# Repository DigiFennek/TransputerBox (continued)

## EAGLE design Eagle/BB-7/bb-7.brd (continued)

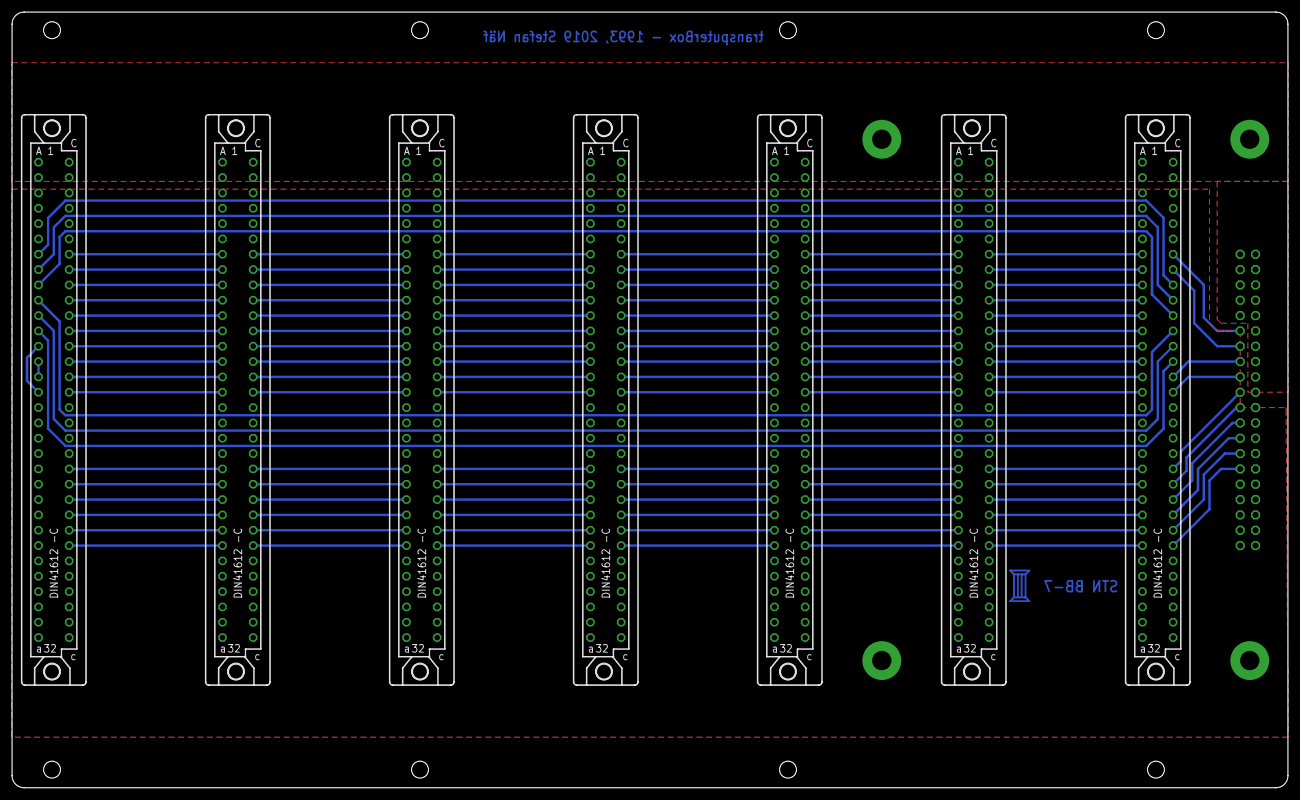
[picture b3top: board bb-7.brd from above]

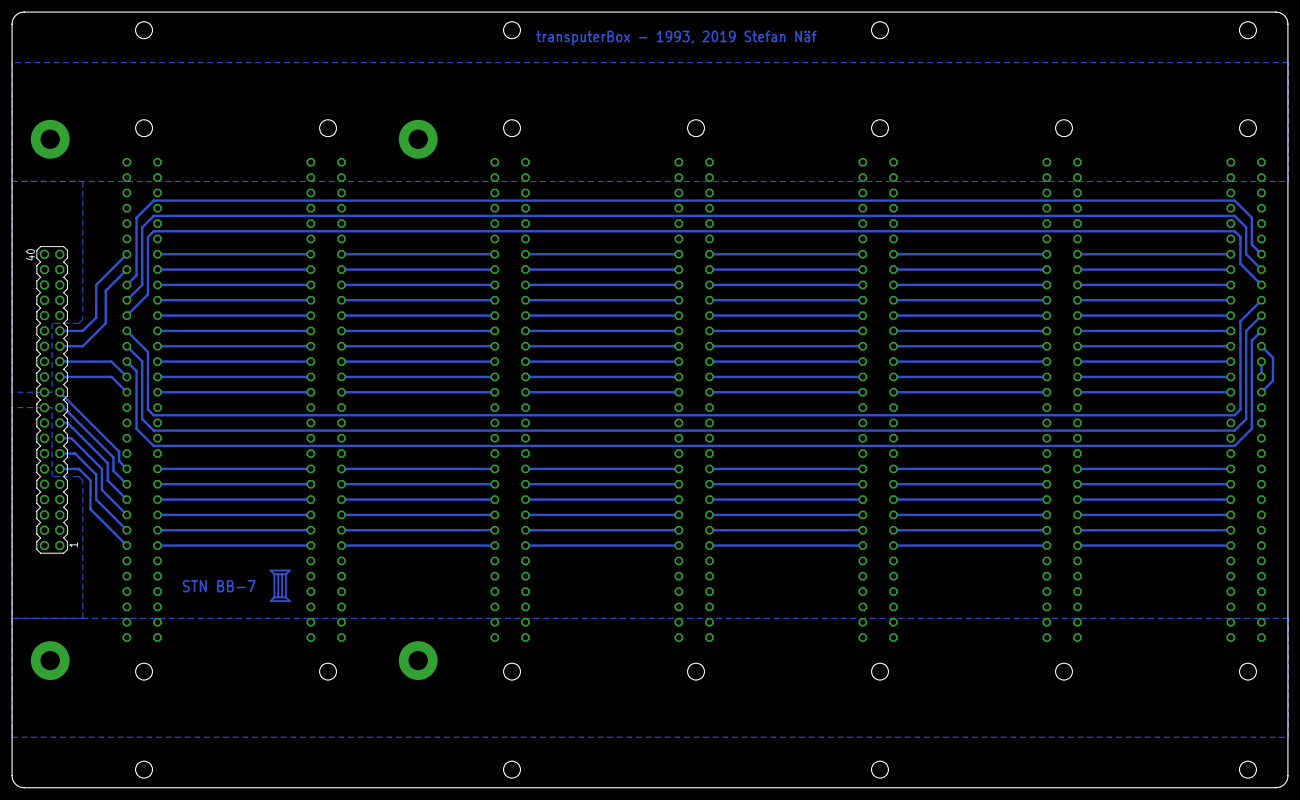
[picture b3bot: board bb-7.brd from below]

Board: 2 copper layers, 211.4 x 128.5 mm, 13 parts (2 on the bottom side), 116 nets.

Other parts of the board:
U$1: LOGO

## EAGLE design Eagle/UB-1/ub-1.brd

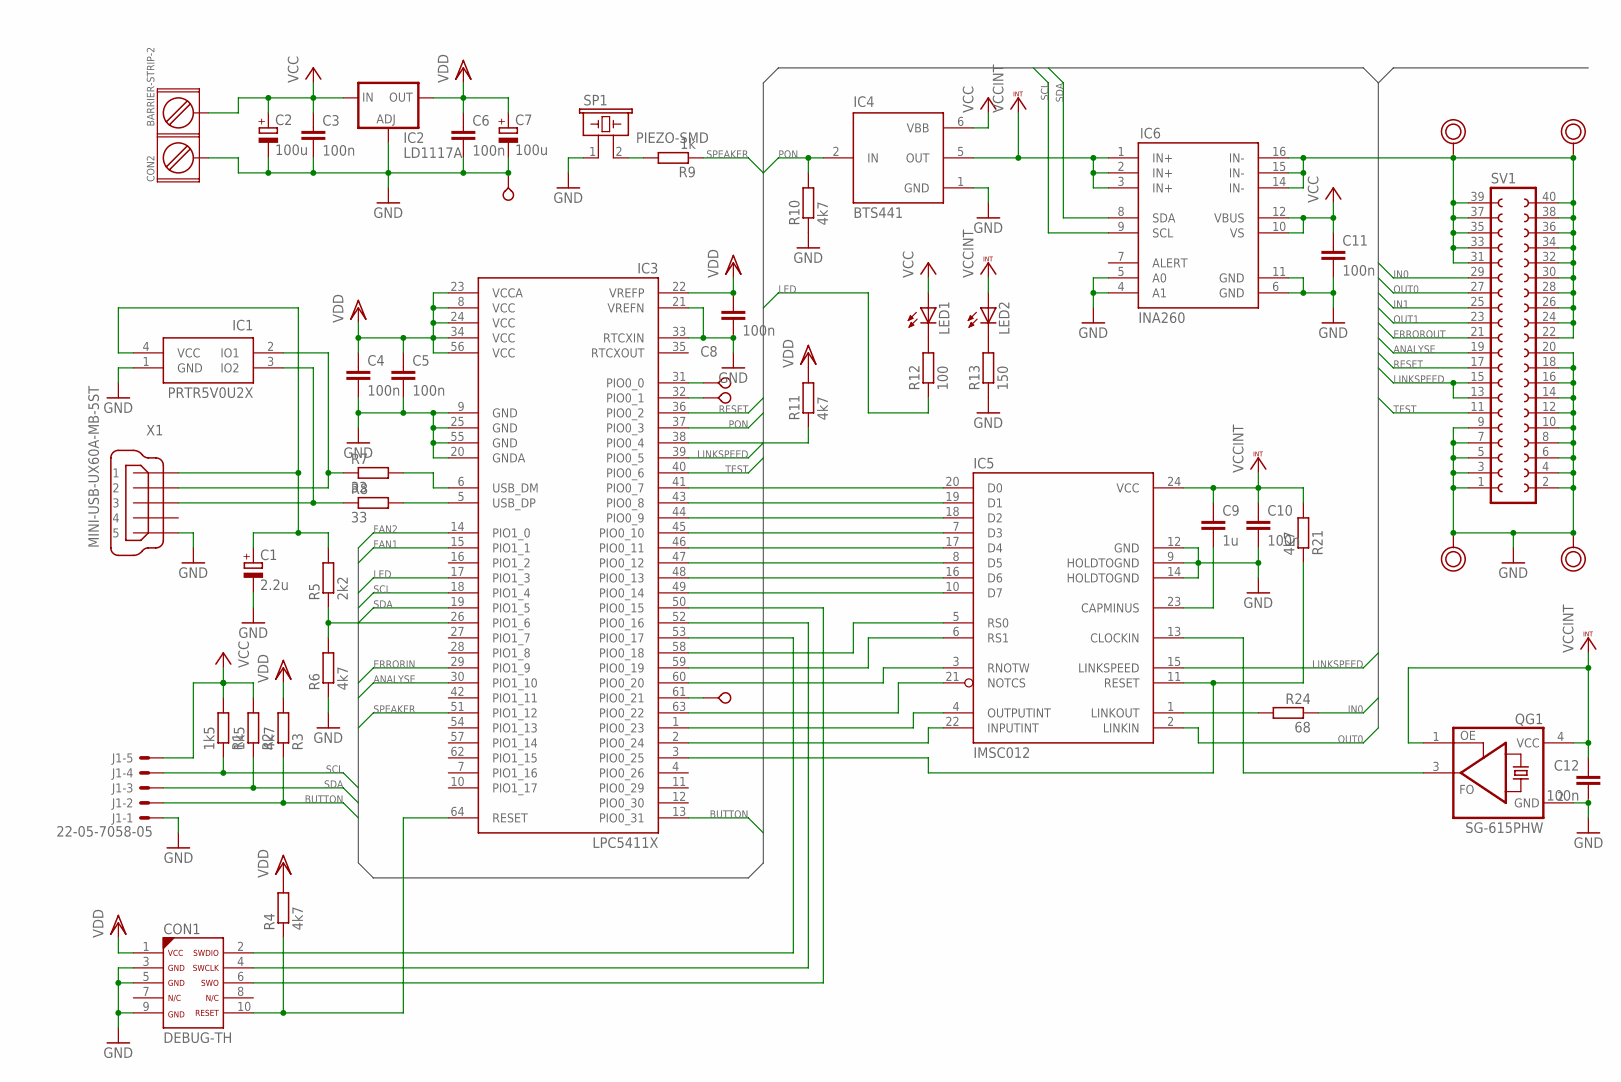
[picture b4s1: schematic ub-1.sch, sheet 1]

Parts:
C1: 2.2u; SMC_B; DIGIKEY 478-3880-1-ND
C2, C7: 100u; SMC_B; DIGIKEY 478-5801-1-ND
C3, C4, C5, C6, C8, C10, C11, C12: 100n; C1206; DIGIKEY 478-10855-1-ND
C9: 1u; C1206; DIGIKEY 478-1567-1-ND
CON1: DEBUG-TH; DIGIKEY 1175-1627-ND
CON2: BARRIER-STRIP-2; DIGIKEY WM13929-ND
IC1: PRTR5V0U2X; SOT143; DIGIKEY 1727-3884-1-ND
IC2: LD1117A; SOT223; DIGIKEY 497-1228-1-ND
IC3: LPC5411X; LQPF64; DIGIKEY 568-13034-ND
IC4: BTS441; TO263-4; DIGIKEY BTS441TGATMA1CT-ND
IC5: IMSC012; DIL24-3
IC6: INA260; TSSOP-16; DIGIKEY 296-47777-1-ND
J1: 22-05-7058-05; 7395-05; DIGIKEY WM2787-ND
LED1, LED2: LEDSMT1206; 1206; DIGIKEY 160-1404-1-ND
QG1: SG-615PHW; SG-615
R1, R2: 1k5; R1206; DIGIKEY CR1206-FX-1501ELFCT-ND
R3, R4, R6, R10, R11, R21: 4k7; R1206; DIGIKEY CR1206-FX-4701ELFCT-ND
R5: 2k2; R1206; DIGIKEY CR1206-FX-2201ELFCT-ND
R7, R8: 33; R1206; DIGIKEY CRS1206-FX-33R0ELFCT-ND
R9: 1k; R1206; DIGIKEY CR1206-FX-1001ELFCT-ND
R12: 100; R1206; DIGIKEY CR1206-FX-1000ELFCT-ND
R13: 150; R1206; DIGIKEY CR1206-FX-1500ELFCT-ND
R24: 68; R1206; DIGIKEY CR1206-FX-68R0ELFCT-ND
SCREW1, SCREW2, SCREW3, SCREW4: POWERPAD
SP1: PIEZO-SMD; DIGIKEY 490-9647-1-ND
SV1: FE20-2
TP1, TP2, TP3, TP4: TESTPOINT; VERO_TP
X1: MINI-USB-UX60A-MB-5ST; UX60A-MB-5ST; DIGIKEY H2961CT-ND

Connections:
ANALYSE: IC3.30 (PIO1_10), SV1.19; also elsewhere on the board
BUTTON: IC3.13 (PIO0_31), J1.2, R3.1
ERRORIN: IC3.29 (PIO1_9); also elsewhere on the board
ERROROUT: SV1.21; also elsewhere on the board
FAN1: IC3.15 (PIO1_1); also elsewhere on the board
FAN2: IC3.14 (PIO1_0); also elsewhere on the board
GND: C1.-, C2.-, C3.2, C4.2, C5.2, C6.2, C7.-, C8.2, C10.2, C11.2, C12.2, CON1.3, CON1.5, CON1.9, CON2.1, IC1.1 (GND), IC2.1 (ADJ), IC3.9 (GND), IC3.20 (GNDA), IC3.21 (VREFN), IC3.25 (GND), IC3.33 (RTCXIN), IC3.55 (GND), IC4.1 (GND), IC5.9 (HOLDTOGND), IC5.12 (GND), IC5.14 (HOLDTOGND), IC6.4 (A1), IC6.5 (A0), IC6.6 (GND), IC6.11 (GND), J1.1, QG1.2 (GND), R6.1, R10.1, R13.1, SCREW2.P$1, SCREW4.P$1, SP1.1, SV1.1, SV1.2, SV1.3, SV1.4, SV1.5, SV1.6, SV1.7, SV1.8, SV1.9, SV1.10, SV1.12, SV1.14, SV1.16, SV1.18, SV1.20, TP3.P$1, X1.5; also elsewhere on the board
IN0: R24.1, SV1.29
IN1: SV1.25; also elsewhere on the board
LED: IC3.17 (PIO1_3), R12.1
LINKSPEED: IC3.39 (PIO0_5), IC5.15 (LINKSPEED), SV1.13, SV1.15
unnamed: CON1.2, IC3.53 (PIO0_17)
unnamed: IC3.31 (PIO0_0), TP1.P$1
unnamed: CON1.4, IC3.52 (PIO0_16)
unnamed: CON1.10, IC3.64 (RESET), R4.1
unnamed: IC3.26 (PIO1_6), R5.1, R6.2
unnamed: IC3.5 (USB_DP), R8.2
unnamed: IC3.6 (USB_DM), R7.2
unnamed: IC6.14 (IN-), IC6.15 (IN-), IC6.16 (IN-), SCREW1.P$1, SCREW3.P$1, SV1.22, SV1.24, SV1.26, SV1.28, SV1.30, SV1.31, SV1.32, SV1.33, SV1.34, SV1.35, SV1.36, SV1.37, SV1.38, SV1.39, SV1.40
unnamed: IC3.41 (PIO0_7), IC5.20 (D0)
unnamed: IC3.32 (PIO0_1), TP2.P$1
unnamed: IC3.61 (PIO0_21), TP4.P$1
unnamed: IC5.1 (LINKOUT), R24.2
unnamed: IC3.43 (PIO0_8), IC5.19 (D1)
unnamed: IC3.44 (PIO0_9), IC5.18 (D2)
unnamed: IC3.45 (PIO0_10), IC5.7 (D3)
unnamed: IC3.46 (PIO0_11), IC5.17 (D4)
unnamed: IC3.47 (PIO0_12), IC5.8 (D5)
unnamed: IC3.48 (PIO0_13), IC5.16 (D6)
unnamed: IC3.49 (PIO0_14), IC5.10 (D7)
unnamed: IC3.60 (PIO0_20), IC5.3 (RNOTW)
unnamed: IC3.59 (PIO0_19), IC5.6 (RS1)
unnamed: IC3.58 (PIO0_18), IC5.5 (RS0)
unnamed: IC3.1 (PIO0_23), IC5.4 (OUTPUTINT)
unnamed: IC3.2 (PIO0_24), IC5.22 (INPUTINT)
unnamed: IC3.63 (PIO0_22), IC5.21 (NOTCS)
unnamed: IC5.13 (CLOCKIN), QG1.3 (FO)
unnamed: C9.2, IC5.23 (CAPMINUS)
unnamed: IC1.2 (IO1), R7.1, X1.2
unnamed: IC1.3 (IO2), R8.1, X1.3
unnamed: LED2.C, R13.2
unnamed: R9.2, SP1.2
unnamed: LED1.C, R12.2
unnamed: CON1.6, IC3.50 (PIO0_15)
unnamed: IC3.38 (PIO0_4), R11.1
unnamed: IC3.3 (PIO0_25), IC5.11 (RESET), R21.1
OUT0: IC5.2 (LINKIN), SV1.27
OUT1: SV1.23; also elsewhere on the board
PON: IC3.37 (PIO0_3), IC4.2 (IN), R10.2; also elsewhere on the board
RESET: IC3.36 (PIO0_2), SV1.17; also elsewhere on the board
SCL: IC3.18 (PIO1_4), IC6.9 (SCL), J1.4, R1.1
SDA: IC3.19 (PIO1_5), IC6.8 (SDA), J1.3, R2.1
SPEAKER: IC3.51 (PIO1_12), R9.1
TEST: IC3.40 (PIO0_6), SV1.11
VCC: C2.+, C3.1, C11.1, CON2.2, IC2.3 (IN), IC4.6 (VBB), IC6.10 (VS), IC6.12 (VBUS), J1.5, LED1.A, R1.2, R2.2; also elsewhere on the board
VCCINT: C9.1, C10.1, C12.1, IC4.5 (OUT), IC5.24 (VCC), IC6.1 (IN+), IC6.2 (IN+), IC6.3 (IN+), LED2.A, QG1.1 (OE), QG1.4 (VCC), R21.2; also elsewhere on the board
VDD: C4.1, C5.1, C6.1, C7.+, C8.1, CON1.1, IC2.2 (OUT), IC3.8 (VCC), IC3.22 (VREFP), IC3.23 (VCCA), IC3.24 (VCC), IC3.34 (VCC), IC3.56 (VCC), R3.2, R4.2, R11.2
VUSB: C1.+, IC1.4 (VCC), R5.2, X1.1

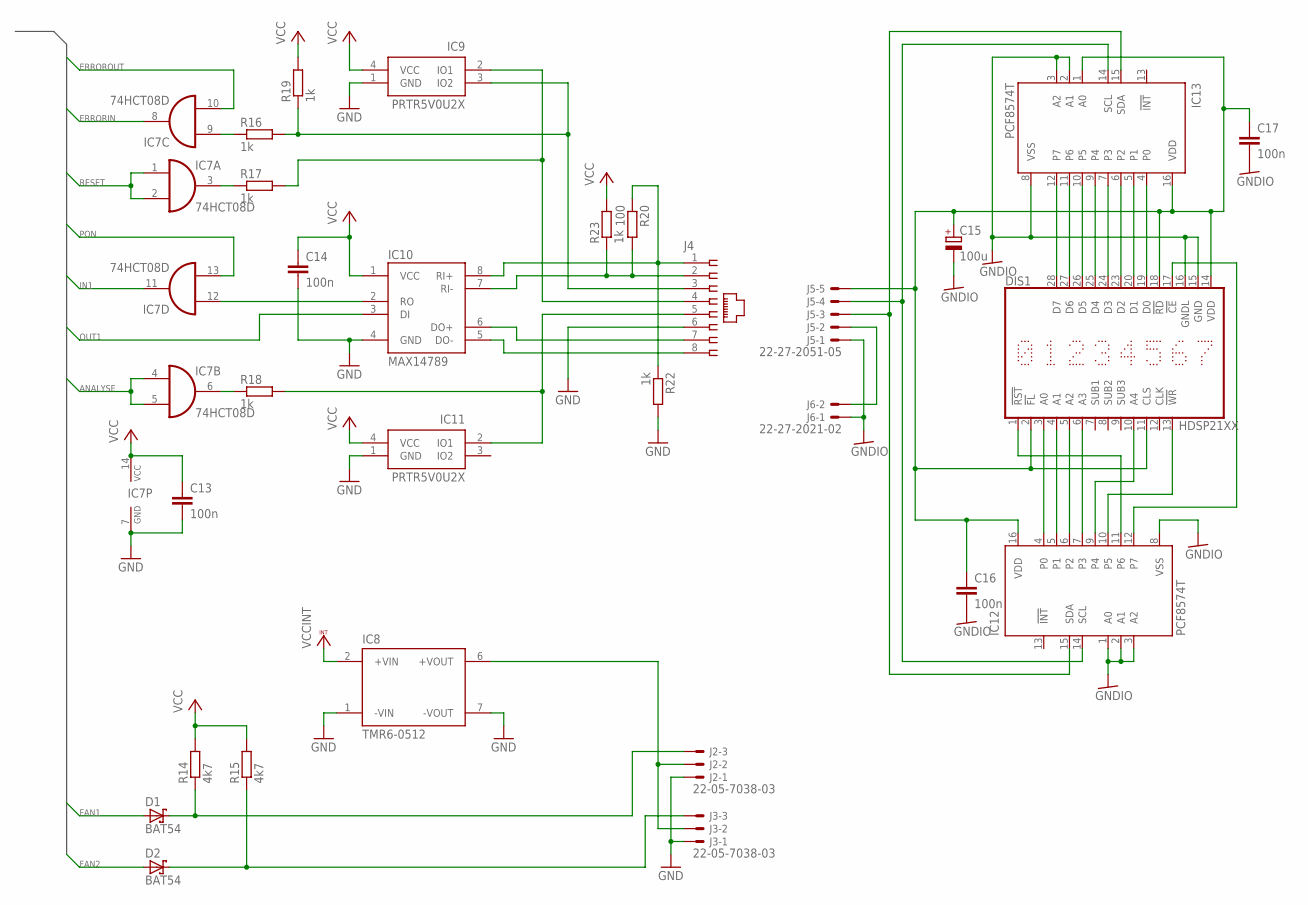
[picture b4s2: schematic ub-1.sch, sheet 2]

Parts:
C13, C14, C16, C17: 100n; C1206; DIGIKEY 478-10855-1-ND
C15: 100u; SMC_B; DIGIKEY 478-5801-1-ND
D1, D2: BAT54; SOT23; DIGIKEY BAT54FSCT-ND
DIS1: HDSP21XX; DIGIKEY 516-1161-5-ND
IC7: 74HCT08D; SO14; DIGIKEY 296-14862-1-ND
IC8: TMR6-0512; DIGIKEY 1951-2391-ND
IC9, IC11: PRTR5V0U2X; SOT143; DIGIKEY 1727-3884-1-ND
IC10: MAX14789; SO8; DIGIKEY MAX14789EGSA+-ND
IC12, IC13: PCF8574T; SO16W; DIGIKEY 568-1077-1-ND
J2, J3: 22-05-7038-03; 7395-03; DIGIKEY WM2785-ND
J4: 555164-1; DIGIKEY A31442-ND
J5: 22-27-2051-05; 6410-05; DIGIKEY WM4114-ND
J6: 22-27-2021-02; 6410-02; DIGIKEY WM4111-ND
R14, R15: 4k7; R1206; DIGIKEY CR1206-FX-4701ELFCT-ND
R16, R17, R18, R19, R22, R23: 1k; R1206; DIGIKEY CR1206-FX-1001ELFCT-ND
R20: 100; R1206; DIGIKEY CR1206-FX-1000ELFCT-ND

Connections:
ANALYSE: IC7.4 (I0), IC7.5 (I1); also elsewhere on the board
ERRORIN: IC7.8 (O); also elsewhere on the board
ERROROUT: IC7.10 (I1); also elsewhere on the board
FAN1: D1.1 (A); also elsewhere on the board
FAN2: D2.1 (A); also elsewhere on the board
GND: C13.2, C14.2, IC7.7 (GND), IC8.1 (-VIN), IC8.7 (-VOUT), IC9.1 (GND), IC10.4 (GND), IC11.1 (GND), J2.1, J3.1, J4.6, R22.2; also elsewhere on the board
GNDIO: C15.-, C16.2, C17.2, DIS1.15 (GND), DIS1.16 (GNDL), IC12.1 (A0), IC12.2 (A1), IC12.3 (A2), IC12.8 (VSS), IC13.2 (A1), IC13.3 (A2), IC13.8 (VSS), J5.1, J6.1
IN1: IC7.11 (O); also elsewhere on the board
unnamed: DIS1.3 (A0), IC12.4 (P0)
unnamed: DIS1.19 (D0), IC13.4 (P0)
unnamed: DIS1.20 (D1), IC13.5 (P1)
unnamed: DIS1.23 (D2), IC13.6 (P2)
unnamed: DIS1.24 (D3), IC13.7 (P3)
unnamed: DIS1.25 (D4), IC13.9 (P4)
unnamed: DIS1.26 (D5), IC13.10 (P5)
unnamed: DIS1.27 (D6), IC13.11 (P6)
unnamed: DIS1.28 (D7), IC13.12 (P7)
unnamed: DIS1.4 (A1), IC12.5 (P1)
unnamed: DIS1.5 (A2), IC12.6 (P2)
unnamed: DIS1.6 (A3), IC12.7 (P3)
unnamed: DIS1.10 (A4), IC12.9 (P4)
unnamed: J5.2, J6.2
unnamed: C15.+, C16.1, C17.1, DIS1.2 (!FL), DIS1.11 (CLS), DIS1.14 (VDD), DIS1.18 (!RD), IC12.16 (VDD), IC13.1 (A0), IC13.16 (VDD), J5.5
unnamed: DIS1.1 (!RST), IC12.11 (P6)
unnamed: DIS1.13 (!WR), IC12.10 (P5)
unnamed: IC12.14 (SCL), IC13.14 (SCL), J5.4
unnamed: DIS1.17 (!CE), IC12.12 (P7)
unnamed: IC12.15 (SDA), IC13.15 (SDA), J5.3
unnamed: IC10.8 (RI+), J4.1, R20.1, R22.1
unnamed: IC10.7 (RI-), J4.2, R20.2, R23.1
unnamed: IC10.5 (DO-), J4.8
unnamed: IC10.6 (DO+), J4.7
unnamed: IC7.6 (O), R18.1
unnamed: IC7.3 (O), R17.1
unnamed: IC7.9 (I0), R16.1
unnamed: IC9.3 (IO2), J4.3, R16.2, R19.1
unnamed: IC9.2 (IO1), J4.4, R17.2
unnamed: IC11.2 (IO1), J4.5, R18.2
unnamed: IC7.12 (I0), IC10.2 (RO)
unnamed: D2.3 (C), J3.3, R15.1
unnamed: D1.3 (C), J2.3, R14.1
unnamed: IC8.6 (+VOUT), J2.2, J3.2
OUT1: IC10.3 (DI); also elsewhere on the board
PON: IC7.13 (I1); also elsewhere on the board
RESET: IC7.1 (I0), IC7.2 (I1); also elsewhere on the board
VCC: C13.1, C14.1, IC7.14 (VCC), IC9.4 (VCC), IC10.1 (VCC), IC11.4 (VCC), R14.2, R15.2, R19.2, R23.2; also elsewhere on the board
VCCINT: IC8.2 (+VIN); also elsewhere on the board

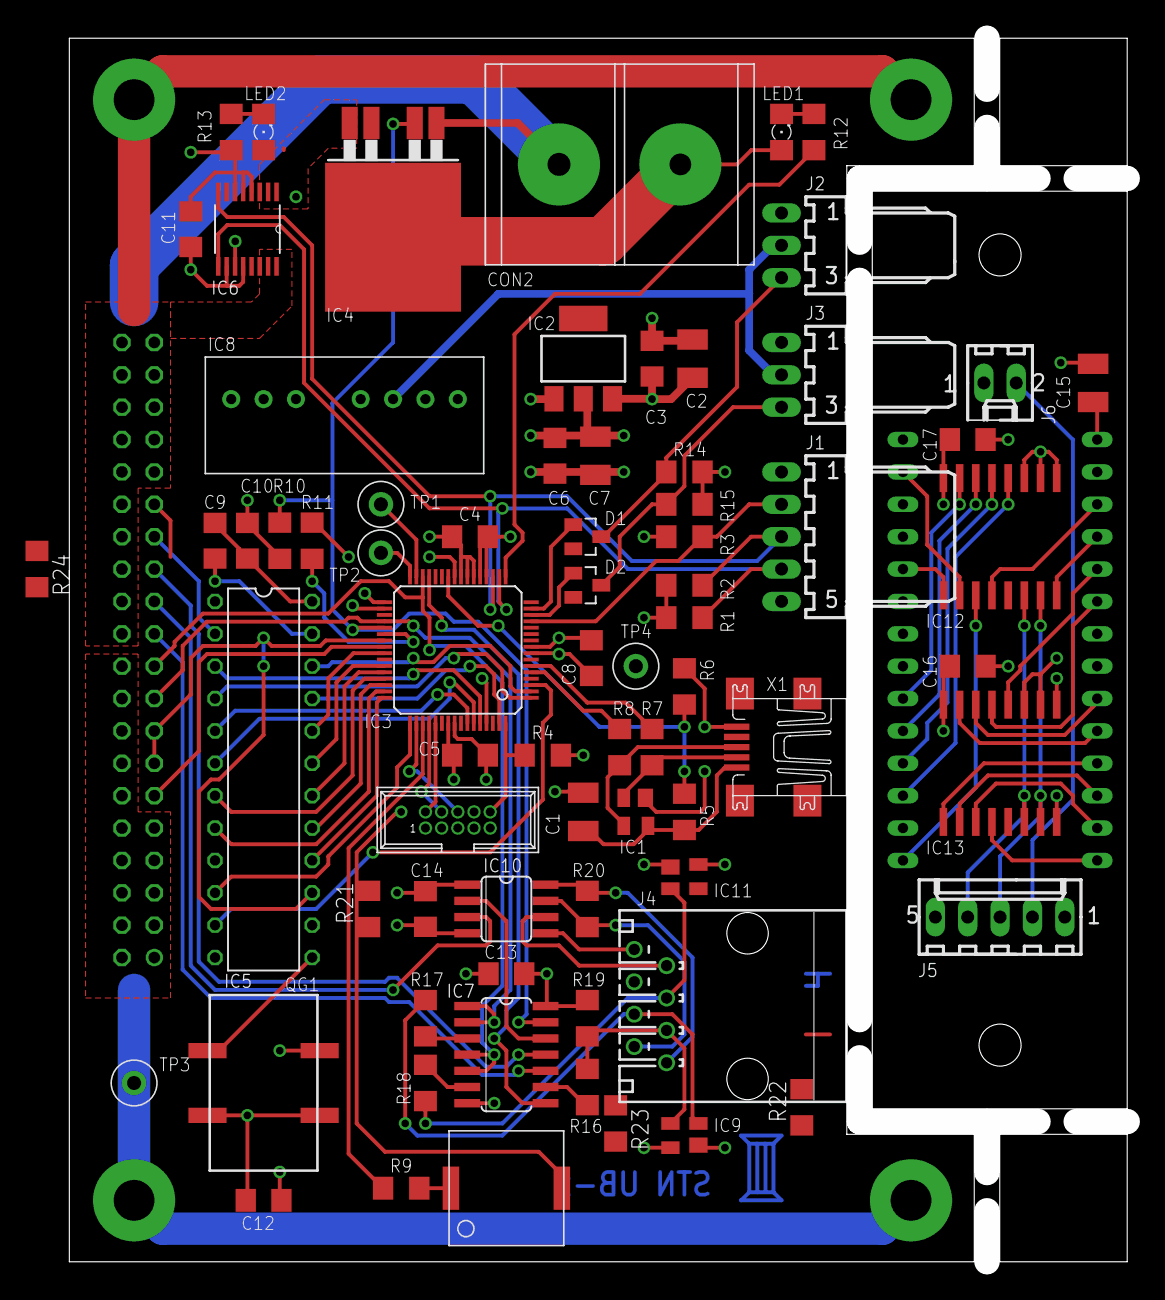
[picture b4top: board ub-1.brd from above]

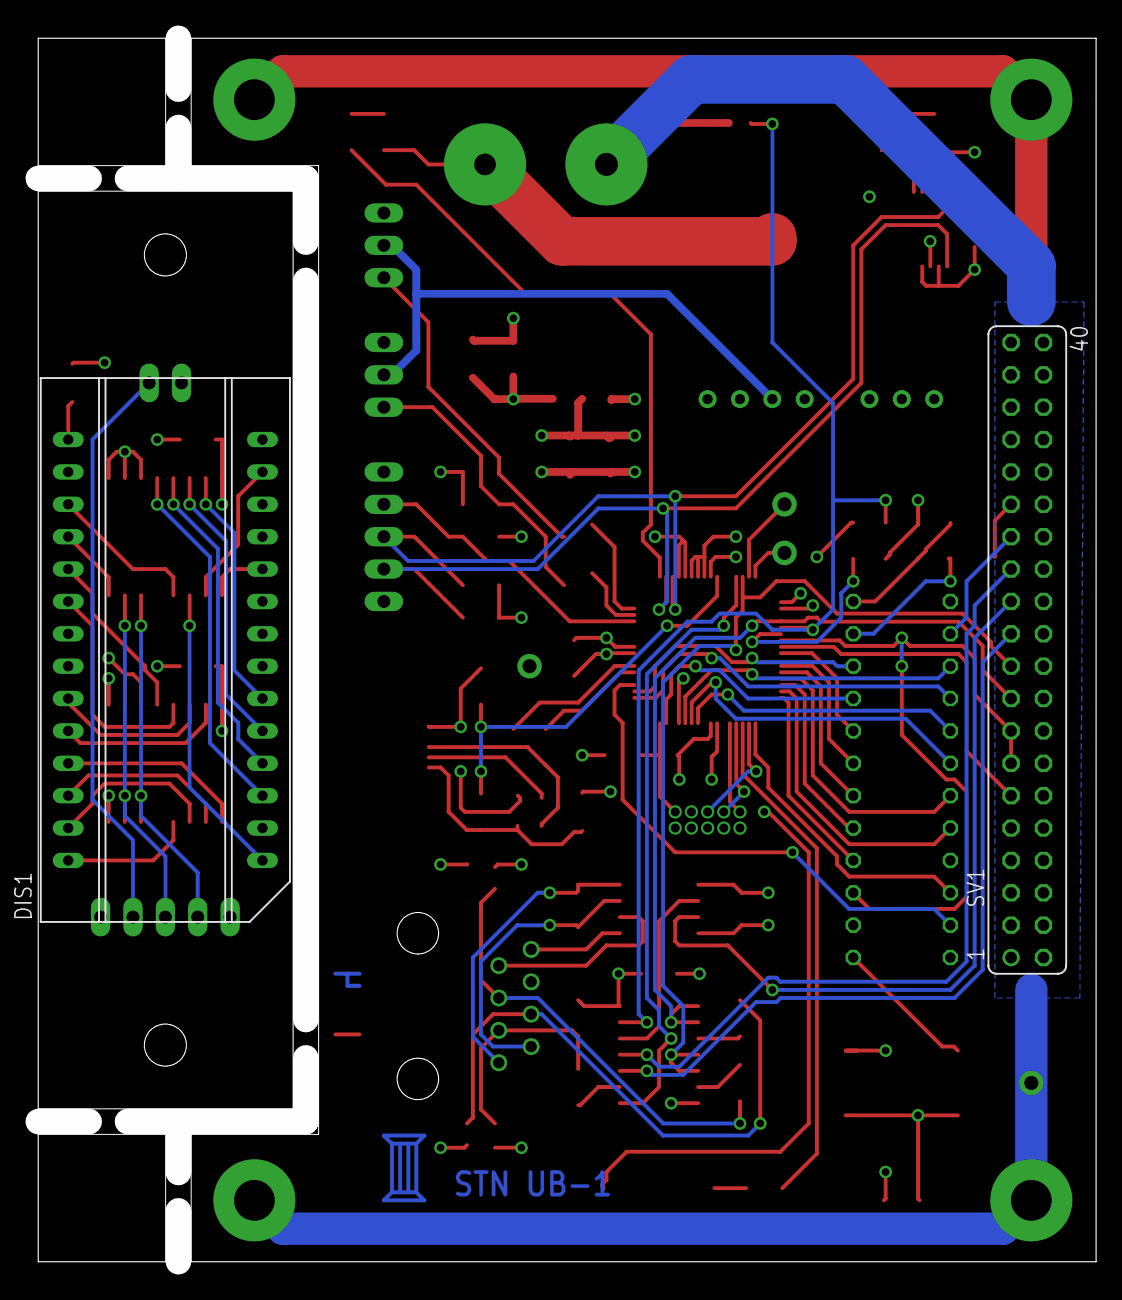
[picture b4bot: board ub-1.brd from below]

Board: 4 copper layers, 83.0 x 96.0 mm, 81 parts (3 on the bottom side), 93 nets.

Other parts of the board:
U$5: LAYER14
U$6: LOGO

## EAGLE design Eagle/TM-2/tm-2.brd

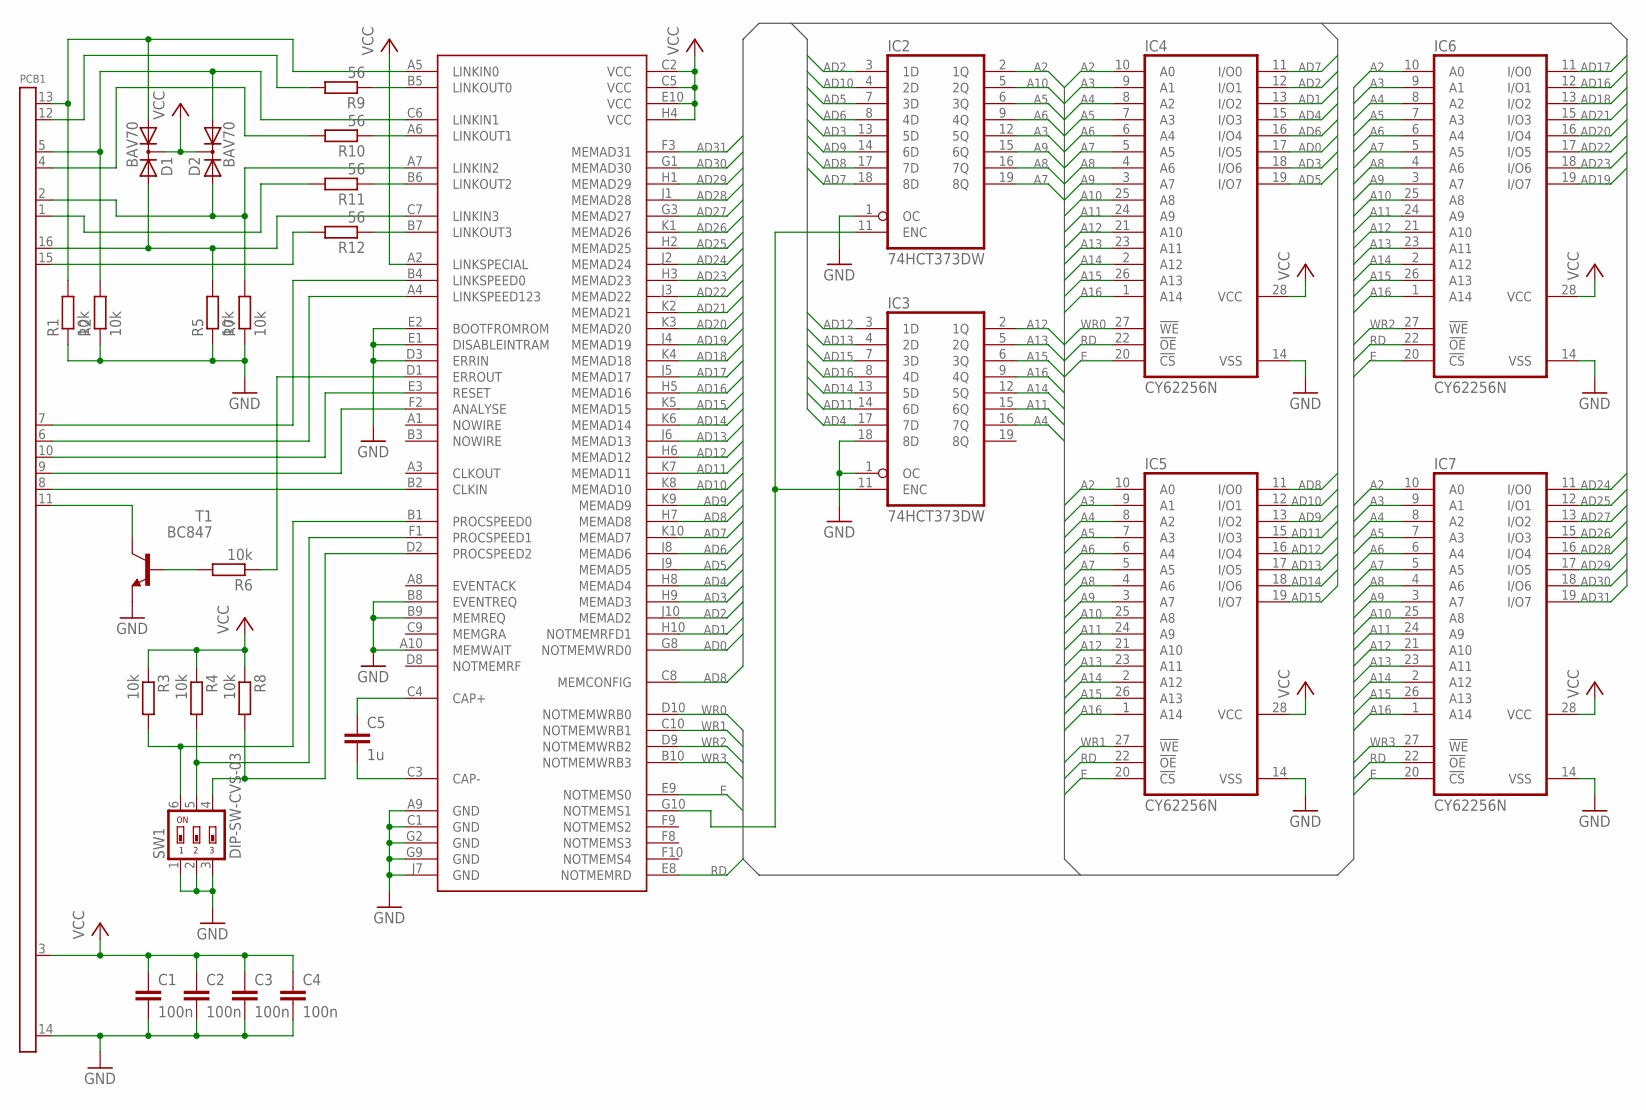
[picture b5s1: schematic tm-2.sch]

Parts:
C1, C2, C3, C4: 100n; C1206
C5: 1u; C1206
D1, D2: BAV70; SOT23
IC1: IMST800; PGA84
IC2, IC3: 74HCT373DW; SO20W
IC4, IC5, IC6, IC7: CY62256N; SOP28N
PCB1: TRAM-1-PCB
R1, R2, R3, R4, R5, R6, R7, R8: 10k; R1206
R9, R10, R11, R12: 56; R1206
SW1: DIP-SW-CVS-03
T1: BC847; SOT23

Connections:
A2: IC2.2 (1Q), IC4.10 (A0), IC5.10 (A0), IC6.10 (A0), IC7.10 (A0)
A3: IC2.12 (5Q), IC4.9 (A1), IC5.9 (A1), IC6.9 (A1), IC7.9 (A1)
A4: IC3.16 (7Q), IC4.8 (A2), IC5.8 (A2), IC6.8 (A2), IC7.8 (A2)
A5: IC2.6 (3Q), IC4.7 (A3), IC5.7 (A3), IC6.7 (A3), IC7.7 (A3)
A6: IC2.9 (4Q), IC4.6 (A4), IC5.6 (A4), IC6.6 (A4), IC7.6 (A4)
A7: IC2.19 (8Q), IC4.5 (A5), IC5.5 (A5), IC6.5 (A5), IC7.5 (A5)
A8: IC2.16 (7Q), IC4.4 (A6), IC5.4 (A6), IC6.4 (A6), IC7.4 (A6)
A9: IC2.15 (6Q), IC4.3 (A7), IC5.3 (A7), IC6.3 (A7), IC7.3 (A7)
A10: IC2.5 (2Q), IC4.25 (A8), IC5.25 (A8), IC6.25 (A8), IC7.25 (A8)
A11: IC3.15 (6Q), IC4.24 (A9), IC5.24 (A9), IC6.24 (A9), IC7.24 (A9)
A12: IC3.2 (1Q), IC4.21 (A10), IC5.21 (A10), IC6.21 (A10), IC7.21 (A10)
A13: IC3.5 (2Q), IC4.23 (A11), IC5.23 (A11), IC6.23 (A11), IC7.23 (A11)
A14: IC3.12 (5Q), IC4.2 (A12), IC5.2 (A12), IC6.2 (A12), IC7.2 (A12)
A15: IC3.6 (3Q), IC4.26 (A13), IC5.26 (A13), IC6.26 (A13), IC7.26 (A13)
A16: IC3.9 (4Q), IC4.1 (A14), IC5.1 (A14), IC6.1 (A14), IC7.1 (A14)
AD0: IC1.G8 (NOTMEMWRD0), IC4.17 (I/O5)
AD1: IC1.H10 (NOTMEMRFD1), IC4.13 (I/O2)
AD2: IC1.J10 (MEMAD2), IC2.3 (1D), IC4.12 (I/O1)
AD3: IC1.H9 (MEMAD3), IC2.13 (5D), IC4.18 (I/O6)
AD4: IC1.H8 (MEMAD4), IC3.17 (7D), IC4.15 (I/O3)
AD5: IC1.J9 (MEMAD5), IC2.7 (3D), IC4.19 (I/O7)
AD6: IC1.J8 (MEMAD6), IC2.8 (4D), IC4.16 (I/O4)
AD7: IC1.K10 (MEMAD7), IC2.18 (8D), IC4.11 (I/O0)
AD8: IC1.C8 (MEMCONFIG), IC1.H7 (MEMAD8), IC2.17 (7D), IC5.11 (I/O0)
AD9: IC1.K9 (MEMAD9), IC2.14 (6D), IC5.13 (I/O2)
AD10: IC1.K8 (MEMAD10), IC2.4 (2D), IC5.12 (I/O1)
AD11: IC1.K7 (MEMAD11), IC3.14 (6D), IC5.15 (I/O3)
AD12: IC1.H6 (MEMAD12), IC3.3 (1D), IC5.16 (I/O4)
AD13: IC1.J6 (MEMAD13), IC3.4 (2D), IC5.17 (I/O5)
AD14: IC1.K6 (MEMAD14), IC3.13 (5D), IC5.18 (I/O6)
AD15: IC1.K5 (MEMAD15), IC3.7 (3D), IC5.19 (I/O7)
AD16: IC1.H5 (MEMAD16), IC3.8 (4D), IC6.12 (I/O1)
AD17: IC1.J5 (MEMAD17), IC6.11 (I/O0)
AD18: IC1.K4 (MEMAD18), IC6.13 (I/O2)
AD19: IC1.J4 (MEMAD19), IC6.19 (I/O7)
AD20: IC1.K3 (MEMAD20), IC6.16 (I/O4)
AD21: IC1.K2 (MEMAD21), IC6.15 (I/O3)
AD22: IC1.J3 (MEMAD22), IC6.17 (I/O5)
AD23: IC1.H3 (MEMAD23), IC6.18 (I/O6)
AD24: IC1.J2 (MEMAD24), IC7.11 (I/O0)
AD25: IC1.H2 (MEMAD25), IC7.12 (I/O1)
AD26: IC1.K1 (MEMAD26), IC7.15 (I/O3)
AD27: IC1.G3 (MEMAD27), IC7.13 (I/O2)
AD28: IC1.J1 (MEMAD28), IC7.16 (I/O4)
AD29: IC1.H1 (MEMAD29), IC7.17 (I/O5)
AD30: IC1.G1 (MEMAD30), IC7.18 (I/O6)
AD31: IC1.F3 (MEMAD31), IC7.19 (I/O7)
E: IC1.E9 (NOTMEMS0), IC4.20 (!CS), IC5.20 (!CS), IC6.20 (!CS), IC7.20 (!CS)
GND: C1.2, C2.2, C3.2, C4.2, IC1.A9 (GND), IC1.A10 (MEMWAIT), IC1.B8 (EVENTREQ), IC1.B9 (MEMREQ), IC1.C1 (GND), IC1.D3 (ERRIN), IC1.E1 (DISABLEINTRAM), IC1.E2 (BOOTFROMROM), IC1.G2 (GND), IC1.G9 (GND), IC1.J7 (GND), IC2.1 (OC), IC2.10 (GND), IC3.1 (OC), IC3.10 (GND), IC3.18 (8D), IC4.14 (VSS), IC5.14 (VSS), IC6.14 (VSS), IC7.14 (VSS), PCB1.14 (GND), R1.1, R2.1, R5.1, R7.1, SW1.1, SW1.2, SW1.3, T1.2 (E)
unnamed: IC1.G10 (NOTMEMS1), IC2.11 (ENC), IC3.11 (ENC)
unnamed: IC1.B5 (LINKOUT0), R9.1
unnamed: C5.1, IC1.C4 (CAP+)
unnamed: C5.2, IC1.C3 (CAP-)
unnamed: IC1.A6 (LINKOUT1), R10.1
unnamed: IC1.B6 (LINKOUT2), R11.1
unnamed: IC1.B7 (LINKOUT3), R12.1
unnamed: PCB1.4 (LINK1OUT), R10.2
unnamed: PCB1.12 (LINK0OUT), R9.2
unnamed: D2.2 (A2), IC1.A7 (LINKIN2), PCB1.2 (LINK2IN), R7.2
unnamed: D2.1 (A1), IC1.C6 (LINKIN1), PCB1.5 (LINK1IN), R2.2
unnamed: D1.1 (A1), IC1.A5 (LINKIN0), PCB1.13 (LINK0IN), R1.2
unnamed: PCB1.1 (LINK2OUT), R11.2
unnamed: D1.2 (A2), IC1.C7 (LINKIN3), PCB1.16 (LINK3IN), R5.2
unnamed: PCB1.15 (LINK3OUT), R12.2
unnamed: IC1.D1 (ERROUT), R6.1
unnamed: IC1.E3 (RESET), PCB1.10 (RESET)
unnamed: IC1.F2 (ANALYSE), PCB1.9 (ANALYSE)
unnamed: IC1.B2 (CLKIN), PCB1.8 (CLOCKIN)
unnamed: IC1.A4 (LINKSPEED123), PCB1.6 (LINKSPEEDA)
unnamed: IC1.B4 (LINKSPEED0), PCB1.7 (LINKSPEEDB)
unnamed: IC1.B1 (PROCSPEED0), R3.2, SW1.6
unnamed: PCB1.11 (NOTERROR), T1.3 (C)
unnamed: R6.2, T1.1 (B)
unnamed: IC1.F1 (PROCSPEED1), R4.2, SW1.5
unnamed: IC1.D2 (PROCSPEED2), R8.2, SW1.4
RD: IC1.E8 (NOTMEMRD), IC4.22 (!OE), IC5.22 (!OE), IC6.22 (!OE), IC7.22 (!OE)
VCC: C1.1, C2.1, C3.1, C4.1, D1.3 (C), D2.3 (C), IC1.A2 (LINKSPECIAL), IC1.C2 (VCC), IC1.C5 (VCC), IC1.E10 (VCC), IC1.H4 (VCC), IC2.20 (VCC), IC3.20 (VCC), IC4.28 (VCC), IC5.28 (VCC), IC6.28 (VCC), IC7.28 (VCC), PCB1.3 (VCC), R3.1, R4.1, R8.1
WR0: IC1.D10 (NOTMEMWRB0), IC4.27 (!WE)
WR1: IC1.C10 (NOTMEMWRB1), IC5.27 (!WE)
WR2: IC1.D9 (NOTMEMWRB2), IC6.27 (!WE)
WR3: IC1.B10 (NOTMEMWRB3), IC7.27 (!WE)

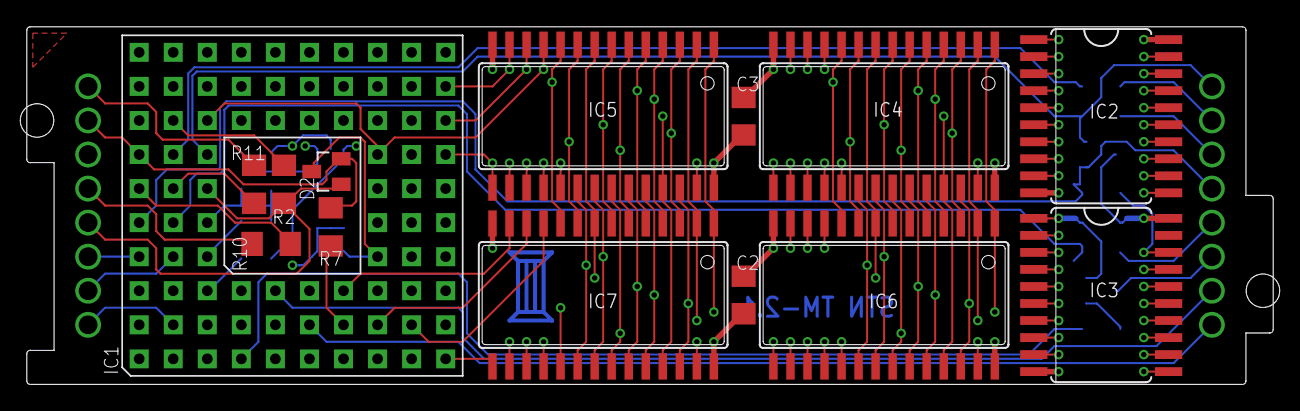
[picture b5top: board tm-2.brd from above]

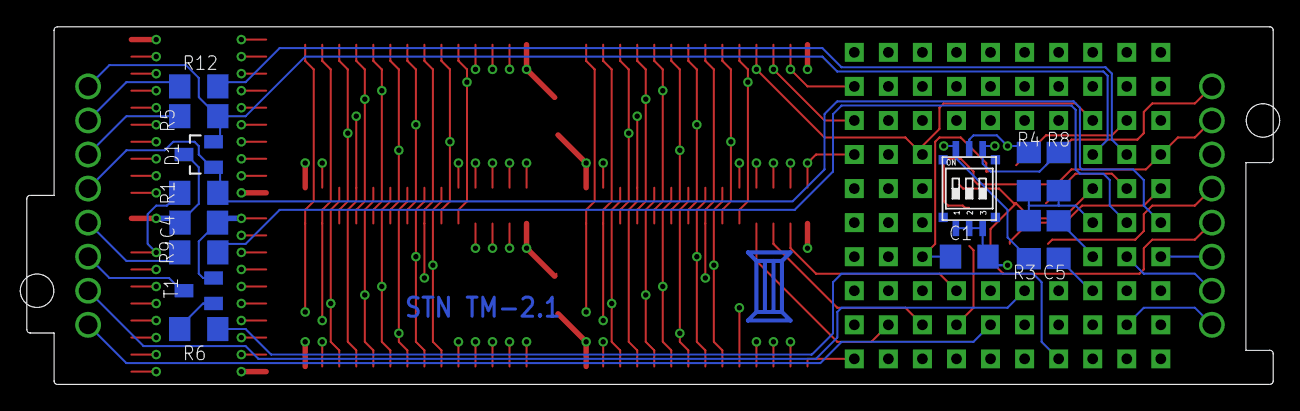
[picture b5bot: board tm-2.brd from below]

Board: 6 copper layers, 93.0 x 26.7 mm, 30 parts (15 on the bottom side), 81 nets.

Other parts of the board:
U$2: LOGO

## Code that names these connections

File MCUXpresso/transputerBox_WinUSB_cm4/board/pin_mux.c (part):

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- {pin_num: '12', pin_signal: PIO0_30/FC1_TXD_SCL_MISO/SCT0_OUT3/CTIMER0_MAT2/CTIMER0_CAP2/ADC0_1, label: SCL1, identifier: SCL;SCL1}
- {pin_num: '13', pin_signal: PIO0_31/PDM0_CLK/FC2_CTS_SDA_SSEL0/CTIMER2_CAP2/CTIMER0_CAP3/CTIMER0_MAT3/ADC0_2, label: Button, identifier: BUTTON}
- {pin_num: '14', pin_signal: PIO1_0/PDM0_DATA/FC2_RTS_SCL_SSEL1/CTIMER3_MAT1/CTIMER0_CAP0/ADC0_3, label: Fan Tacho 1, identifier: FAN_TACHO_1}
- {pin_num: '15', pin_signal: PIO1_1/SWO/SCT0_OUT4/FC5_SSEL2/FC4_TXD_SCL_MISO/ADC0_4, label: Fan Tacho 2, identifier: FAN_TACHO_2}
- {pin_num: '16', pin_signal: PIO1_2/MCLK/FC7_SSEL3/SCT0_OUT5/FC5_SSEL3/FC4_RXD_SDA_MOSI/ADC0_5}
- {pin_num: '17', pin_signal: PIO1_3/FC7_SSEL2/SCT0_OUT6/FC3_SCK/CTIMER0_CAP1/USB0_UP_LED/ADC0_6, label: LED, identifier: LED}
- {pin_num: '18', pin_signal: PIO1_4/PDM1_CLK/FC7_RTS_SCL_SSEL1/SCT0_OUT7/FC3_TXD_SCL_MISO/CTIMER0_MAT1/ADC0_7}
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- {pin_num: '27', pin_signal: PIO1_7/FC7_RXD_SDA_MOSI_DATA/CTIMER1_MAT2/CTIMER1_CAP2/ADC0_10}
- {pin_num: '28', pin_signal: PIO1_8/FC7_TXD_SCL_MISO_WS/CTIMER1_MAT3/CTIMER1_CAP3/ADC0_11}
- {pin_num: '29', pin_signal: PIO1_9/FC3_RXD_SDA_MOSI/CTIMER0_CAP2/USB0_UP_LED, label: Error, identifier: ERROR}
- {pin_num: '30', pin_signal: PIO1_10/FC6_TXD_SCL_MISO_WS/SCT0_OUT4/FC1_SCK/USB0_FRAME, label: Analyse, identifier: ANALYSE}
- {pin_num: '36', pin_signal: PIO0_2/FC0_CTS_SDA_SSEL0/FC2_SSEL3/CTIMER2_CAP1, label: Reset, identifier: RESET}
- {pin_num: '37', pin_signal: PIO0_3/FC0_RTS_SCL_SSEL1/FC2_SSEL2/CTIMER1_MAT3, label: Power On, identifier: PON}
- {pin_num: '38', pin_signal: PIO0_4/FC0_SCK/FC3_SSEL2/CTIMER0_CAP2}
- {pin_num: '39', pin_signal: PIO0_5/FC6_RXD_SDA_MOSI_DATA/SCT0_OUT6/CTIMER0_MAT0, label: Link Speed, identifier: LINK_SPEED}
- {pin_num: '40', pin_signal: PIO0_6/FC6_TXD_SCL_MISO_WS/CTIMER0_MAT1/UTICK_CAP0, label: Test, identifier: TEST}
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- {pin_num: '47', pin_signal: PIO0_12/FC3_RXD_SDA_MOSI/FC6_TXD_SCL_MISO_WS/CTIMER2_MAT3, label: C012 D5, identifier: C012_D5}
- {pin_num: '48', pin_signal: PIO0_13/FC3_TXD_SCL_MISO/SCT0_OUT4/CTIMER2_MAT0, label: C012 D6, identifier: C012_D6}
- {pin_num: '49', pin_signal: PIO0_14/FC3_CTS_SDA_SSEL0/SCT0_OUT5/CTIMER2_MAT1/FC1_SCK, label: C012 D7, identifier: C012_D7}
- {pin_num: '50', pin_signal: PIO0_15/FC3_RTS_SCL_SSEL1/SWO/CTIMER2_MAT2/FC4_SCK}
- {pin_num: '51', pin_signal: PIO1_12/FC5_RXD_SDA_MOSI/CTIMER1_MAT0/FC7_SCK/UTICK_CAP2, label: Speaker, identifier: SPEAKER}
- {pin_num: '52', pin_signal: PIO0_16/FC3_SSEL2/FC6_CTS_SDA_SSEL0/CTIMER3_MAT1/SWCLK}
- {pin_num: '53', pin_signal: PIO0_17/FC3_SSEL3/FC6_RTS_SCL_SSEL1/CTIMER3_MAT2/SWDIO}
- {pin_num: '54', pin_signal: PIO1_13/FC5_TXD_SCL_MISO/CTIMER1_MAT1/FC7_RXD_SDA_MOSI_DATA}
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- options: {callFromInitBoot: 'true', prefix: BOARD_, coreID: cm4, enableClock: 'true'}
- pin_list:
  - {pin_num: '14', peripheral: GPIO, signal: 'PIO1, 0', pin_signal: PIO1_0/PDM0_DATA/FC2_RTS_SCL_SSEL1/CTIMER3_MAT1/CTIMER0_CAP0/ADC0_3, direction: INPUT}
  - {pin_num: '15', peripheral: GPIO, signal: 'PIO1, 1', pin_signal: PIO1_1/SWO/SCT0_OUT4/FC5_SSEL2/FC4_TXD_SCL_MISO/ADC0_4, direction: INPUT}
  - {pin_num: '36', peripheral: GPIO, signal: 'PIO0, 2', pin_signal: PIO0_2/FC0_CTS_SDA_SSEL0/FC2_SSEL3/CTIMER2_CAP1, direction: OUTPUT, gpio_init_state: 'false',
    mode: inactive, slew_rate: standard}
  - {pin_num: '37', peripheral: GPIO, signal: 'PIO0, 3', pin_signal: PIO0_3/FC0_RTS_SCL_SSEL1/FC2_SSEL2/CTIMER1_MAT3, direction: OUTPUT, mode: inactive}
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  - {pin_num: '17', peripheral: GPIO, signal: 'PIO1, 3', pin_signal: PIO1_3/FC7_SSEL2/SCT0_OUT6/FC3_SCK/CTIMER0_CAP1/USB0_UP_LED/ADC0_6, direction: OUTPUT, gpio_init_state: 'false',
    mode: inactive}
  - {pin_num: '26', peripheral: USB0, signal: USB_VBUS, pin_signal: PIO1_6/FC7_SCK/CTIMER1_CAP2/CTIMER1_MAT2/USB0_VBUS/ADC0_9}
  - {pin_num: '50', peripheral: SWD, signal: SWO, pin_signal: PIO0_15/FC3_RTS_SCL_SSEL1/SWO/CTIMER2_MAT2/FC4_SCK}
  - {pin_num: '52', peripheral: SWD, signal: SWCLK, pin_signal: PIO0_16/FC3_SSEL2/FC6_CTS_SDA_SSEL0/CTIMER3_MAT1/SWCLK}
  - {pin_num: '53', peripheral: SWD, signal: SWDIO, pin_signal: PIO0_17/FC3_SSEL3/FC6_RTS_SCL_SSEL1/CTIMER3_MAT2/SWDIO}
  - {pin_num: '19', peripheral: FLEXCOMM7, signal: CTS_SDA_SSEL0, pin_signal: PIO1_5/PDM1_DATA/FC7_CTS_SDA_SSEL0/CTIMER1_CAP0/CTIMER1_MAT3/USB0_FRAME/ADC0_8}
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  - {pin_num: '3', peripheral: GPIO, signal: 'PIO0, 25', pin_signal: PIO0_25/FC4_RTS_SCL_SSEL1/FC6_CTS_SDA_SSEL0/CTIMER0_CAP2/CTIMER1_CAP1, direction: OUTPUT, gpio_init_state: 'false',
    i2c_drive: no_init, i2c_filter: disabled}
  - {pin_num: '14', peripheral: PINT, signal: 'PINT, 0', pin_signal: PIO1_0/PDM0_DATA/FC2_RTS_SCL_SSEL1/CTIMER3_MAT1/CTIMER0_CAP0/ADC0_3, identifier: ''}
  - {pin_num: '15', peripheral: PINT, signal: 'PINT, 1', pin_signal: PIO1_1/SWO/SCT0_OUT4/FC5_SSEL2/FC4_TXD_SCL_MISO/ADC0_4, identifier: ''}
  - {pin_num: '61', peripheral: GPIO, signal: 'PIO0, 21', pin_signal: PIO0_21/CLKOUT/FC0_TXD_SCL_MISO/CTIMER3_MAT0, identifier: DEBUG, direction: OUTPUT, gpio_init_state: 'false',
    mode: inactive}
 * BE CAREFUL MODIFYING THIS COMMENT - IT IS YAML SETTINGS FOR TOOLS ***********
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                          (~(IOCON_PIO_FUNC_MASK | IOCON_PIO_DIGIMODE_MASK)))

                         /* Selects pin function.
                          * : PORT015 (pin 50) is configured as SWO. */
                         | IOCON_PIO_FUNC(PIO015_FUNC_ALT2)

                         /* Select Analog/Digital mode.
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
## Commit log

2023-05-30 Sync with local work
2023-06-21 Front panels added
